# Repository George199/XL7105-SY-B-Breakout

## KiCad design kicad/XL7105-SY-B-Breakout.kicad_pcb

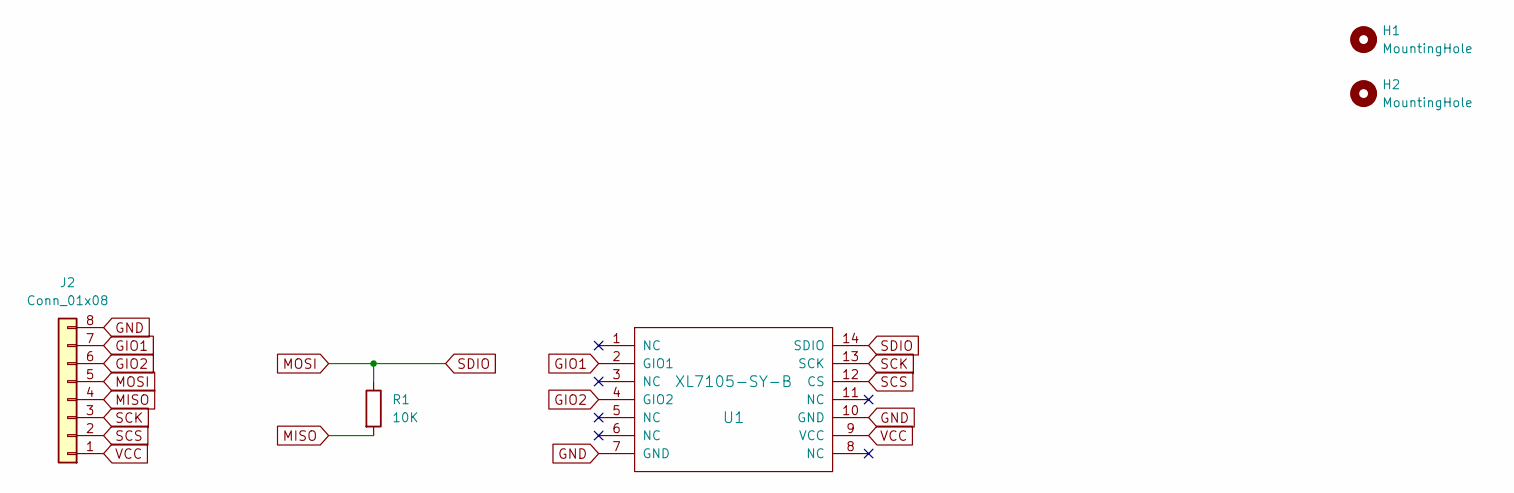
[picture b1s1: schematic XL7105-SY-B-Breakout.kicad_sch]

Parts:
H1, H2: MountingHole; MountingHole_2.2mm_M2
J2: Conn_01x08; PinHeader_1x08_P2.54mm_Horizontal
R1: 10K; R_0603_1608Metric_Pad0.98x0.95mm_HandSolder
U1: XL7105-SY-B

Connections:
GIO1: J2.7, U1.2 (GIO1)
GIO2: J2.6, U1.4 (GIO2)
GND: J2.8, U1.7 (GND), U1.10 (GND)
MISO: J2.4, R1.2
MOSI: J2.5, R1.1, U1.14 (SDIO)
SCK: J2.3, U1.13 (SCK)
SCS: J2.2, U1.12 (CS)
VCC: J2.1, U1.9 (VCC)

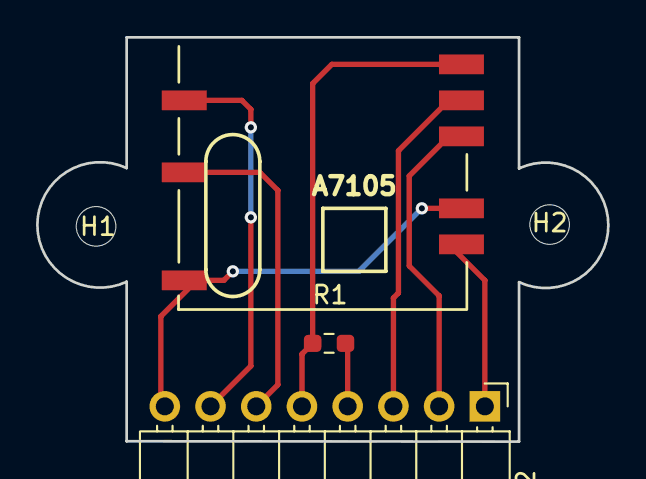
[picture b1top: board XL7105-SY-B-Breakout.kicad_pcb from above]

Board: 2 copper layers, 31.7 x 22.5 mm, 5 parts (0 on the bottom side), 8 nets.
